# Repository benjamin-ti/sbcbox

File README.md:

# sbcbox
SBC-Box (Single Board Computer Box)

This is a collection of code and docs used as a knowledge base for SBCs, in particular for BeagleBone (Black) and Raspberry Pi.

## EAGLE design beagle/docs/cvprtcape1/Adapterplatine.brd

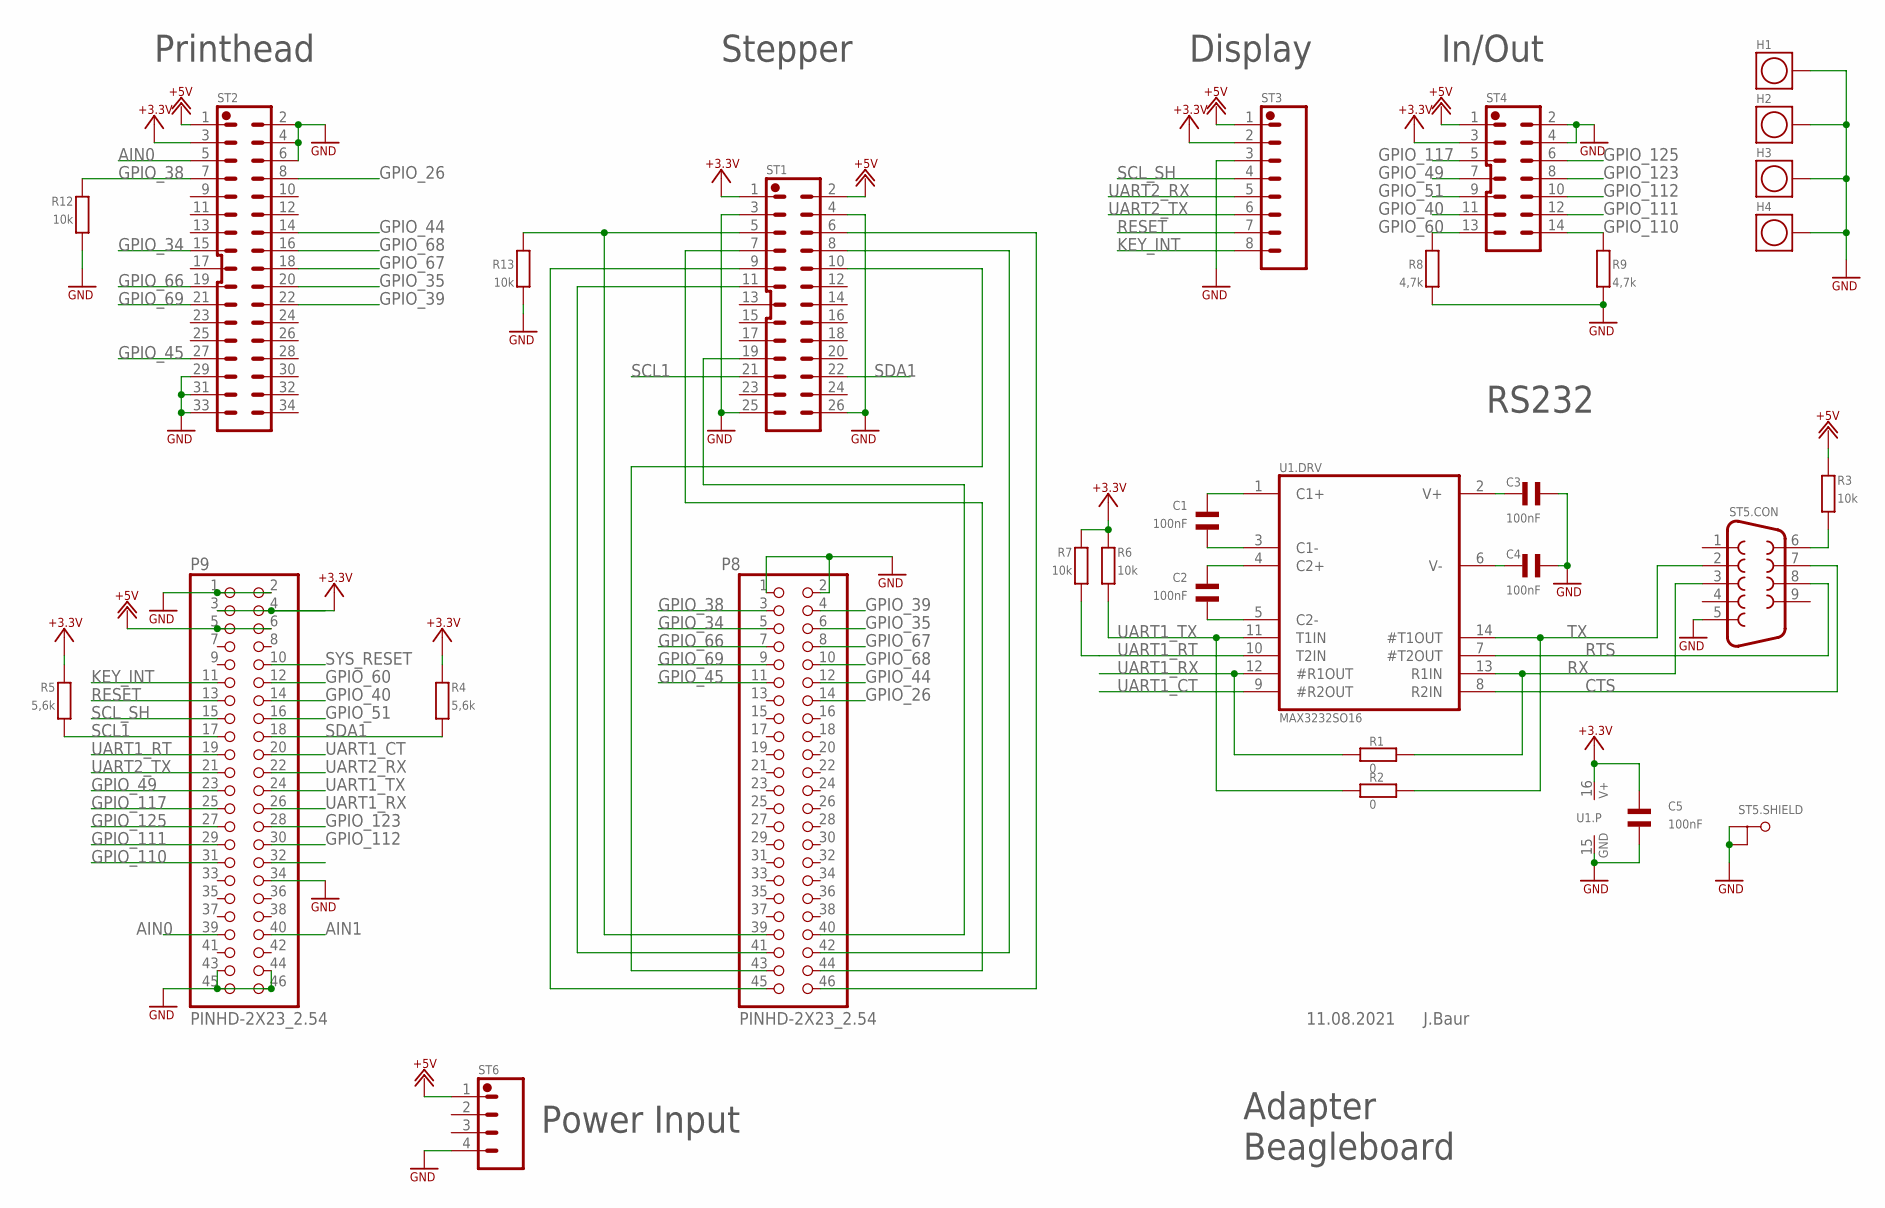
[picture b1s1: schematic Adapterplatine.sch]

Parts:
C1, C2, C3, C4, C5: 100nF; 0603L
H1, H2, H3, H4: HALTERUNG_SQUAREHALTERUNG_SQUARE_6.5_3.5; HALTERUNG_SQUARE_6.5_3.5
P8, P9: PINHD-2X23_2.54; 2X23
R1, R2: 0; 0603L
R3, R6, R7, R12, R13: 10k; 0603L
R4, R5: 5,6k; 0603L
R8, R9: 4,7k; 0603L
ST1: STK-26-2RJST-PHD_26_TH; JST-PHD_26_TH
ST2: STK-34-2R-MJST-PHD_34_TH-D1.0; JST-PHD_34_TH-D1.0
ST3: STK-08-1RJST-PH_8_TH; JST-PH_8_TH
ST4: STK-14-2RJST-PHD_14_TH; JST-PHD_14_TH
ST5: STK-09-SUBD-FSTK-09-SUBD-F-WSI; STK-09-SUBD-F-WSI
ST6: STK-04-1RJST-VH_4_TH; JST-VH_4_TH
U1: MAX3232SO16; SO16

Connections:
+3.3V: C5.P$2 (2), P9.3, P9.4, R4.P$2 (2), R5.P$2 (2), R6.P$2 (2), R7.P$2 (2), ST1.1, ST2.3, ST3.2, ST4.3, U1.16 (V+)
+5V: P9.5, P9.6, R3.P$2 (2), ST1.2, ST2.1, ST3.1, ST4.1, ST6.1
AIN0: P9.39, ST2.5
AIN1: P9.40
CTS: ST5.7, U1.8 (R2IN)
GND: C3.P$1 (1), C4.P$2 (2), C5.P$1 (1), H1.P$1, H2.P$1, H3.P$1, H4.P$1, P8.1, P8.2, P9.1, P9.2, P9.34, P9.43, P9.44, P9.45, P9.46, R8.P$1 (1), R9.P$1 (1), R12.P$1 (1), R13.P$2 (2), ST1.3, ST1.4, ST1.25, ST1.26, ST2.2, ST2.4, ST2.6, ST2.29, ST2.31, ST2.33, ST3.3, ST4.2, ST4.4, ST5.5, ST5.G1 (S1), ST5.G2 (S2), ST6.4, U1.15 (GND)
GPIO_26: P8.14, ST2.8
GPIO_34: P8.5, ST2.15
GPIO_35: P8.6, ST2.20
GPIO_38: P8.3, R12.P$2 (2), ST2.7
GPIO_39: P8.4, ST2.22
GPIO_40: P9.14, ST4.11
GPIO_44: P8.12, ST2.14
GPIO_45: P8.11, ST2.27
GPIO_49: P9.23, ST4.7
GPIO_51: P9.16, ST4.9
GPIO_60: P9.12, R8.P$2 (2), ST4.13
GPIO_66: P8.7, ST2.19
GPIO_67: P8.8, ST2.18
GPIO_68: P8.10, ST2.16
GPIO_69: P8.9, ST2.21
GPIO_110: P9.31, R9.P$2 (2), ST4.14
GPIO_111: P9.29, ST4.12
GPIO_112: P9.30, ST4.10
GPIO_117: P9.25, ST4.5
GPIO_123: P9.28, ST4.8
GPIO_125: P9.27, ST4.6
KEY_INT: P9.11, ST3.8
unnamed: P8.46, ST1.6
unnamed: P8.44, ST1.7
unnamed: P8.42, ST1.8
unnamed: P8.45, ST1.9
unnamed: P8.43, ST1.10
unnamed: P8.41, ST1.11
unnamed: P8.39, R13.P$1 (1), ST1.5
unnamed: P8.40, ST1.19
unnamed: R3.P$1 (1), ST5.6
unnamed: C3.P$2 (2), U1.2 (V+)
unnamed: C4.P$1 (1), U1.6 (V-)
unnamed: C1.P$2 (2), U1.1 (C1+)
unnamed: C1.P$1 (1), U1.3 (C1-)
unnamed: C2.P$2 (2), U1.4 (C2+)
unnamed: C2.P$1 (1), U1.5 (C2-)
RESET: P9.13, ST3.7
RTS: ST5.8, U1.7 (#T2OUT)
RX: R1.P$2 (2), ST5.3, U1.13 (R1IN)
SCL1: P9.17, R5.P$1 (1), ST1.21
SCL_SH: P9.15, ST3.4
SDA1: P9.18, R4.P$1 (1), ST1.22
SYS_RESET: P9.10
TX: R2.P$2 (2), ST5.2, U1.14 (#T1OUT)
UART1_CT: P9.20, U1.9 (#R2OUT)
UART1_RT: P9.19, R7.P$1 (1), U1.10 (T2IN)
UART1_RX: P9.26, R1.P$1 (1), U1.12 (#R1OUT)
UART1_TX: P9.24, R2.P$1 (1), R6.P$1 (1), U1.11 (T1IN)
UART2_RX: P9.22, ST3.5
UART2_TX: P9.21, ST3.6

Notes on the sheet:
Stepper
Printhead
Display
RS232
Adapter Beagleboard
In/Out
Power Input
11.08.2021
J.Baur

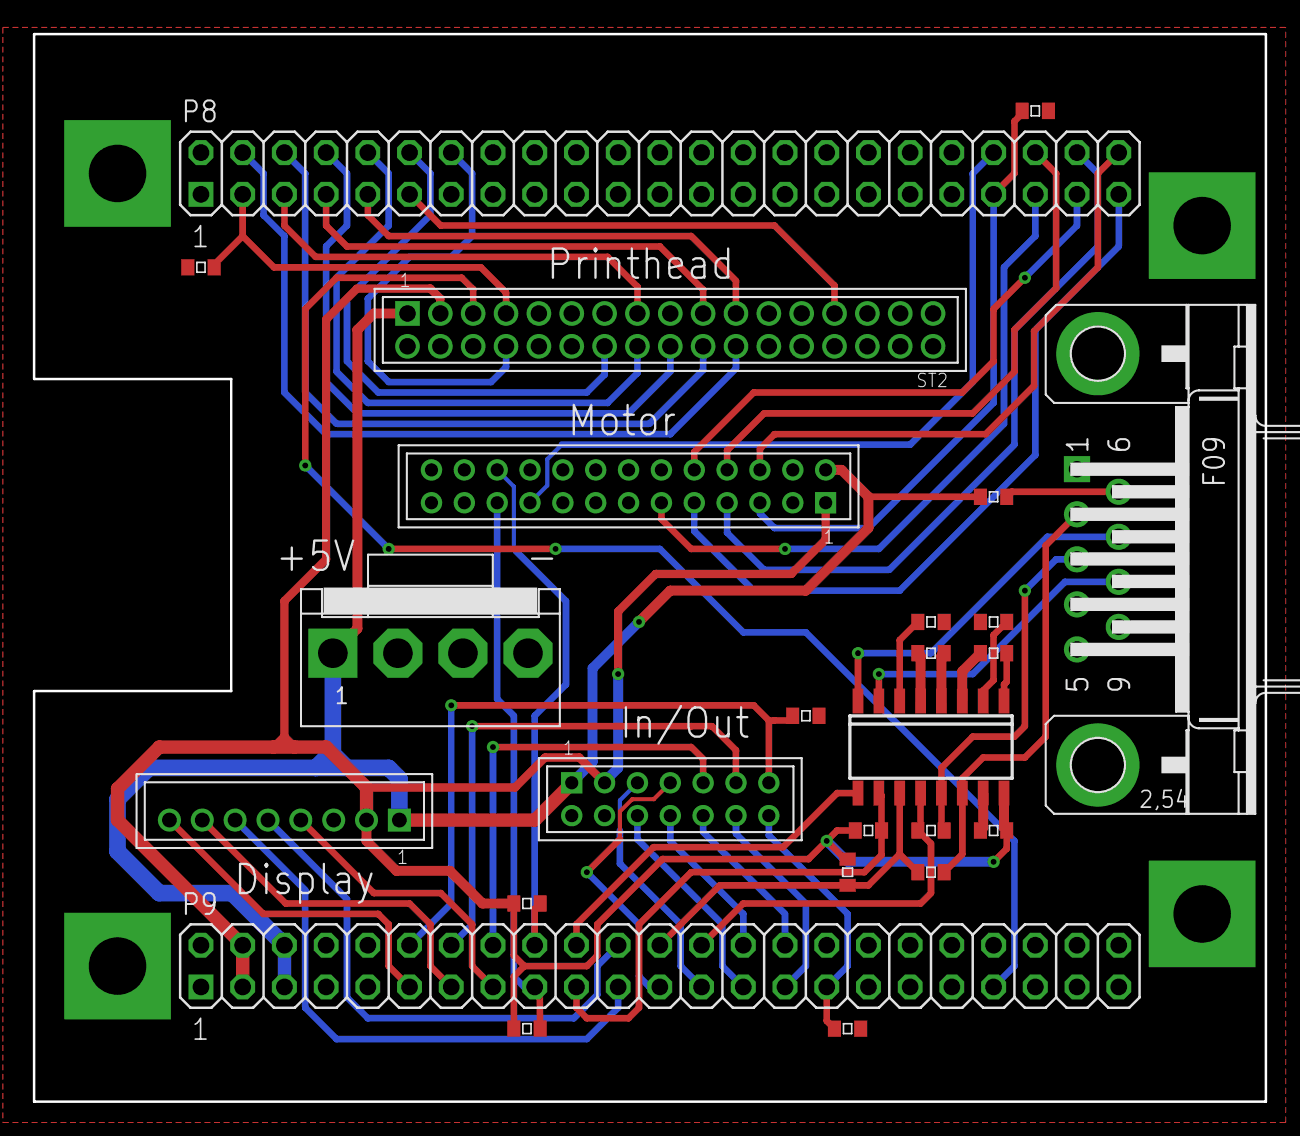
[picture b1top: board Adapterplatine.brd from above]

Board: 2 copper layers, 75.0 x 65.0 mm, 29 parts (0 on the bottom side), 55 nets.

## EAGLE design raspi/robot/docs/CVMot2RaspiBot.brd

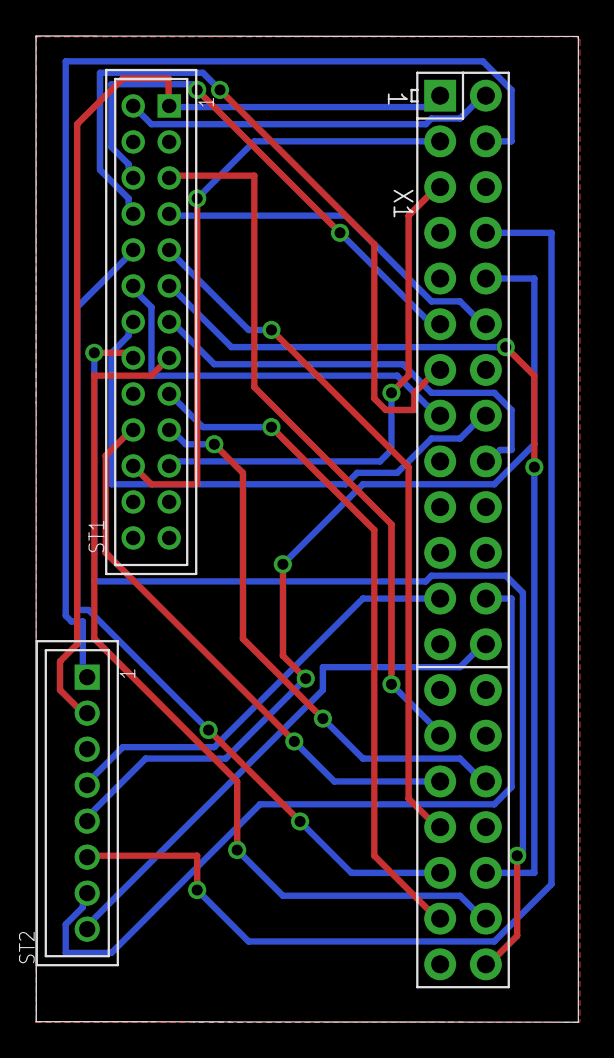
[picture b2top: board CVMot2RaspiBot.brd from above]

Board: 2 copper layers, 30.1 x 54.8 mm, 3 parts (0 on the bottom side), 26 nets.

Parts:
ST1: B26B-PHDSS; JST-PHD_26_TH
ST2: B8B-PH-K-S; JST-PH_8_TH
X1: RASPI_GPIO_B+#_PIN; RASPI_GPIO_B+_PIN

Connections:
GND: ST1.3, ST1.4, ST1.25, ST1.26, ST2.3, X1.6, X1.9, X1.14, X1.20, X1.25, X1.30, X1.34, X1.39
M1_CURRENT: ST1.6, X1.11
M1_DIR: ST1.8, X1.13
M1_STEP: ST1.7, X1.12
MOTOR_RESET: ST1.5, X1.29
unnamed: ST1.9, X1.33
unnamed: ST1.11, X1.36
unnamed: ST1.10, X1.35
unnamed: ST1.12, X1.15
unnamed: ST1.14, X1.16
unnamed: ST1.13, X1.18
unnamed: ST1.15, X1.38
unnamed: ST1.17, X1.37
unnamed: ST1.16, X1.40
unnamed: ST1.19, X1.32
unnamed: ST1.20, X1.31
unnamed: ST2.4, X1.23
unnamed: ST1.2, X1.2
unnamed: ST1.1, ST2.2, X1.1
unnamed: ST1.21, X1.5
unnamed: ST1.22, X1.3
unnamed: ST2.1, X1.4
unnamed: ST2.5, X1.10
unnamed: ST2.6, X1.8
unnamed: ST2.7, X1.24
unnamed: ST2.8, X1.26

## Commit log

2018-06-08 Creating_initial_branch_structure
2018-06-08 Toggle GPIO1
2018-06-09 High Priority Sheduling
2018-06-09 My MMap
2018-06-28 First DMA Example
2018-07-16 1st x86 Hello World Kernel Module
2018-07-17 X86-Kernel-Config
2018-07-21 update x86
2018-07-24 Fehlende Doku nachgereicht
2018-07-24 Erstes Raspi Kernel Module
2018-07-24 Eincheckfehler rückgängig gemacht
2018-09-18 dma_alloc_coherent erster Test
2018-11-21 dmaSimpleCopyMy in kernel module
2018-12-01 DmaSimpleGPIO in KernelModule
2018-12-08 Update docs
2018-12-13 Realtime Linux
2018-12-14 Documents Update
2019-04-03 In mykernel2.c endlich PWM mit DMA geschafft
2020-01-04 Pinning docu added
2020-06-09 yocto 4 raspi - first try
2020-09-22 Property Update
2020-09-22 Projekt-Reorganisation
2020-09-22 BeagleBone Doku
2020-09-22 Beagle GPIO Simple Example
2020-09-22 Update Beagle GPIO Simple Example
2020-09-22 Beagle GPIO Simple Update
2020-09-22 Beagle: gpioHardcore 1st
2020-10-17 Infos für U-Boot für CV-Octavo
2020-11-03 Device-Tree Overlay Example Raspi
2020-11-16 Beagle: GPIO-Hardcore: Jetzt aber richtig
2020-11-16 cvoctavo: Boot-Script and how to compile
2020-11-16 BeagleBone: Doku Update
2020-11-16 BeagleBone: docs update
2020-12-08 Update BeagleBone: BuildRoot docs
2020-12-16 Update buildroot 4 beagle
2020-12-18 bbbrcfg: Ignore .project
2020-12-18 beagle: ignore eclipse config files
2020-12-18 BB-BuildRoot: Add DropBear SSH-Server
2020-12-18 BB-BuildRoot: Add Qt Support
2020-12-20 BB-Buildroot: Higher Target Size to 250M
2020-12-21 BB-Buildroot: Mit Auto-IP (aka Zeroconf aka AVAHI)
2020-12-21 BB-Buildroot: UART2 aktiviert
2020-12-22 BB-Buildroot: Auf BR2_EXTERNAL umgestellt und hello-Applikation als Beispiel für eigenes Package hinzugefügt.
2020-12-22 New: Serial.txt
2020-12-29 BB-Buildroot: Device-Trees in eigene Dateien ausgelagert statt bestehende zu patchen
2020-12-29 BB-Buildroot: Eigene Device-Trees werden jetzt auch per default verwendet
2021-01-08 Neuer Texas-Instruments SGX-Grafik-Treiber (tut aber noch nicht ganz)
2021-01-09 Beagle-Buildroot: Fehler im SGX-Treiber Make Skript behoben
2021-01-09 BB-Buildroot: Patched-Configuration falls meine neuen SGX-Treiber-Packages nicht funktionieren
2021-01-09 BB-Buildroot: SFTP-Server
2021-01-09 BB-Buildroot: Fonts für Qt-Apps
2021-01-12 BB-Buildroot: Add Qt Widgets and QuickControl2, higher Image Size to 512MB
2021-01-13 Sample project for qt
2021-01-13 BB-Buildroot: Linux Kernel 4DCape Touchscreen Support
2021-01-15 BB-Buildroot: Buildroot package to automate the build of our Qt HMI testproject
2021-01-15 BB-Buildroot: 4DCape now selectable with Env-Variable (you could source 4dcape.sh)
2021-01-20 BB-Buildroot: Passing IP Address as a 1st argument to our Qt HMI testproject
2021-01-22 BB-Buildroot: SPI0-Support
2021-01-28 BB-Buildroot: Dynamisches Umschalten zwischen UART und SPI-Funktionen bei P9_21 und P9_22
2021-01-28 git hints
2021-03-12 Raspi: Neues Projekt Relais
2021-03-13 Raspi: New C-Code Projekt for Relais
2021-03-13 Raspi: Relais: Shell-Skripte
2021-03-14 Raspi Doku Update
2021-03-14 Raspi: Neues Projekt Robot
2021-03-14 Raspi: Update Relais, jetzt mit libgpiod
2021-03-14 Raspi: Robot: Jetzt mit MotNT (noch nicht fertig)
2021-03-29 CV Disp Prog Tool: 1. Version
2021-03-29 CV Disp Prog Tool: 2. Version
2021-03-29 CV Disp Prog Tool: Jetzt mit schnellem Programming von 3s
2021-03-31 Erweiterung Device-Tree Universal (Pinmux zur Laufzeit mit pinmux-helper) um P9_27-P9_30 für CV-2Line-Display-Update. Dazu musste auch mcasp im common auf univ umgestellt werden.
2021-03-31 CV Disp Prog Tool: make upload target added
2021-04-14 Angleichung an Namen in Druckerfirmware
2021-04-14 CVDispProg: Fehlerbehebung
2021-04-16 cvdispprog: Compiler auf neue Buildroot-Toolchain
2021-04-25 Robot: Working MotNT with Alternatives
2021-04-30 Robot: Test with HW-PWM
2021-05-02 CV-DispPrint Raw
2021-05-03 CV Print Disp jetzt funktionierend
2021-05-29 Neues Projekt: QEmuBare
2021-05-29 QEmuBare Docs
2021-05-30 QEmuBare Launch Update
2021-06-06 QEmu
2021-06-27 Raspi: Update Doku
2021-06-27 Update Raspi-Doku
2021-07-09 DTS fuer Octavo Development-Board
2021-07-15 CV-Octavo: fw_env-Projekt wegen Probleme von fw_printenv mit bad blocks
2021-07-15 CV-Octavo: fw_env: Originalzustand aus u-boot 2020.01 wiederhergestellt
2021-07-15 CV-Octavo: fw_env: Fix für Valentin Bad-Block Problem
2021-07-15 Raspi JTAG
2021-07-15 Raspi: Neue Adapter-Schaltpläne
2021-07-16 Raspi: Update Schaltpläne
2021-07-17 Anpassung an raspi sysroot path
2021-07-17 Raspi: Neues Projekt MyRaspiDMA
2021-07-18 SimpleDMA Raspi Project Update (scp-update)
2021-07-18 Raspi: Neues Projekt: MyRaspiDMA
2021-07-20 Erster Versuch mit CV-Octavo (Serielle Ausgabe bei U-Boot tut immerhin schon mal)
2021-07-21 CV-Octavo: Nochmalige Überarbeitung von fw_env
2021-07-21 MyRaspiDMA: Test und Anpassung
2021-07-21 Raspi Sysroot-Sync Update
2021-08-01 Raspi: Neue Kernel PWM-DMA Implementierung MyRaspiDMA
2021-08-01 Raspi: Sync_sysroot Update
2021-09-12 Doku fuer Beagle/cvprtcape1
2021-09-22 Beagle: CVPrtCape1-Unterstützung
2021-11-30 Beagle Buildroot: Xenomai-Init
2021-11-30 Beagle Buildroot: Xenomai defconfig
2021-11-30 Beagle: Xenomai Hello World
2021-11-30 Beagle Xenomai Hello World RT Task
2021-12-01 Beagle: Input-Event Beispiel mit Libgpiod
2021-12-01 Input Beispiel, jetzt aber richtig
2021-12-02 BeagelBone Buildroot: Konfigurationsupdate für PRUs
2021-12-02 Beagle: PRU Beispiel Programm
2021-12-04 Beagle: project cleaning: put cvdisp and gpio in own projects
2021-12-04 Beagle: added am3358 manual
2021-12-04 Beagle: remove dead files
2021-12-06 Beagle: Update PRU und Xenomai
2021-12-06 Header-Update
2021-12-07 Beagle, Xenomai: Toggle Pin in RT Task
2021-12-08 Beagle: Update Xenomai PWM example. Add Kernel Module Hello
2021-12-10 Beagle: PWM-Stepper 4 cvprtcape1 example
2021-12-12 Beagle: Improved PRU-Example
2021-12-13 Beagle: Improved GPIO-Motor
2021-12-14 Beagle: New PRU examples
2021-12-14 Beagle: Working PRU RPMsg Example
2021-12-17 Beagle-PRU: host ram access
2021-12-19 Beagle: kernel module with pwm 4 motor with kthreads
2022-01-23 svn2git docs
2022-01-23 update some files
2022-01-25 Update beagle docs
2022-01-25 Beagle Buildroot: Load uboot script over tftp
2022-03-02 BeagleBone AI IPC example
2022-03-02 Update BeagleBone AI IPC Example
2022-03-07 BBAI Device Tree Examples
2022-03-12 Beagle-Buildroot: Support for Octavo Red with 4D-Touch-Cape
2022-03-15 Beagle Buildroot: Rename Sample->QtHello and test2->CVTouchDemo
2022-03-18 Qt for CV-Octavo does boot now
2022-03-24 New BeagleAI-Project IPC HelloWorld
2022-03-24 BeagleAI: Update docu
2022-03-25 BeagleAI: GPIO Hardcore
2022-03-25 BeagleAI: Added System Reference Manual to docs and Update ipc_hello with gpio support
2022-04-29 beagle: multithread-test to test debugger performance
2022-06-10 New BoneAI-Project: ipc_motor
2022-06-10 IPC-Motor: Split in host and ipu1 part
2022-06-11 IPC-Motor: First simple message from host to ipu1
2022-06-12 BoneAI-IPC-Motor: Share RAM between Host and IPU1
2022-06-23 STM32F-Start
2022-10-04 MThread-Test: Remove Output files
2022-10-06 Update Multithread-Test
2022-10-29 cvoctavo filewrite
2022-11-04 filewrite with options
2022-12-09 Update PRU-Examples
2022-12-23 Change Main Eclipse Project Type
2022-12-27 QEmuBare on VersatilePB now with running timer
2023-01-28 QEmuBare2 4 Realview Cortex A8
2023-01-30 IVT for Qemu RealView Cortex A8
2023-01-30 Cortex-A8 docu
2023-02-03 QemuBare2: Debugging works now and with first Timer-Int implementation
2023-02-25 Update raspi sysroot sync
2023-03-20 new project cvoctavo km_fpga
2023-03-20 GPIO-Input Example improved
2023-03-25 New try for DMA-Copy on Am335x. A step forward, but still did not work.
2023-04-07 CV-Octavo KM-Memcpy: First working version
2023-04-21 cvoctavo: working example kernel-module with dma to control gpio
2023-04-21 Beagle Buildroot: Own dts-files in custom dts-path instead of patches
2023-05-06 beagle: new project baremetal
2023-05-10 beagle baremetal: No running with interrupts in JTAG
2023-05-12 Move Qemu bare from raspi to qemu dir
2023-05-23 Beagle: Kernel Module KMMotor. First try with chardrv
2023-05-26 kmmotor: Now with interrupts for gpio and dmtimer but timer int is not working yet
2023-05-27 buildroot cvoctavo test. Näher am original CVOctavo. Für vergleichende Tests.
2023-05-27 own buildroot config for qemu_arm_vexpress
2023-05-28 Eclipse Debug Launcher for debugging uboot with qemu vexpress
2023-05-29 qemu_vexpress_br can now boot from sdcard with uboot
2023-06-05 kmfpga: Start new DMA-Transfer in Callback
2023-06-05 beagle baremetal: UART driver
2023-06-05 Starterware DMA-Copy on base of GPIO LED Blink
2023-06-10 QEmu VExpress: Image-Resize after build
2023-06-10 Update BR-QEmu-VExpress Project
2023-06-11 Better TmpSvn for Uboot/linux in Buildroot
2023-06-12 Update Starterware DMA-Code: Now able to handle GPIO-Event driven DMAs
2023-06-12 Qemu-VExpress: UBoot is now able to boot Linux from sdcard
2023-06-19 Starterware: Double DMA with start over GPIO Works now, thanks to ack on gpio_eoi register
2023-06-19 km_fpga is now also able to repeat a dma
2023-07-03 Adjustments for prtsoft and cvfpgakiti
2023-07-06 Update km_fpga
2023-07-08 km_hello extended with examples to device-tree gpio and char-device communication
2023-07-08 Starterware: DMA-IO now with two strokes
2023-07-08 KMFPGA_AS_KITI
2023-07-14 Corrected typing error
2023-07-19 Example kernel modules now with device tree pin-ctrl
2023-07-19 SvnRepos ignore for TmpSvn for Uboot/linux in Buildroot
2023-07-19 Buildroot-Support in cvoctavo for km_fpga
2023-09-12 Device tree change for CVOctavo DMA experiments
2023-09-12 Support for USB-Ethernet modules in buildroot linux cvoctavo2
2023-09-12 New findings for uboot debug
2023-09-12 Errors in PRU example solved
2023-11-21 Beagle-BareMetal: Second DMTimer-Interrupt with better Interrupt-handling
2023-11-21 Beagle BareMetal: Nested Interrupts
2023-11-24 BareMetal-Readme
2023-11-28 QEmuBare: Simple interrupt flow
2023-11-28 QEmuBare: Vectored interrupt flow sequence
2023-12-01 QEMU-Versatile config for buildroot
2023-12-02 New files Qemu-Int Project
2023-12-03 Running Timer Interrupt for Qemu-Versatile
2023-12-09 QEmu Versatile NoMMMU Startup Scripts
2023-12-22 cvoctavo: More kernel image formats on card for experimenting
2023-12-22 Current status of PRU-Motor (not working)
2023-12-25 Qemu-Raspi2 Config for buildroot
2024-01-01 New Project: QEmuBare-Raspi
2024-01-18 IRQ Experiments
2024-01-22 PRU_Motor with Acceleration
2024-02-22 New PRU-Motor Version
2024-03-15 BBB-Bare-Metal: memory management
2024-03-15 BBB-Baremetal: forgot file
2024-03-28 baremetal: init bss to zero
2024-11-11 DMA Experiments
2024-11-13 Baremetal starts now complete in RAM
2024-11-13 uboot example script for booting baremetal programs
2025-01-14 Starterware example extended for run time tests
2025-01-24 Beagle Baremetal: Disable watchdog for direct booting baremetal.
2025-01-24 beagle buildroot: New config for u-boot baremetal booting
2025-05-15 I/O Test Serial Pins
